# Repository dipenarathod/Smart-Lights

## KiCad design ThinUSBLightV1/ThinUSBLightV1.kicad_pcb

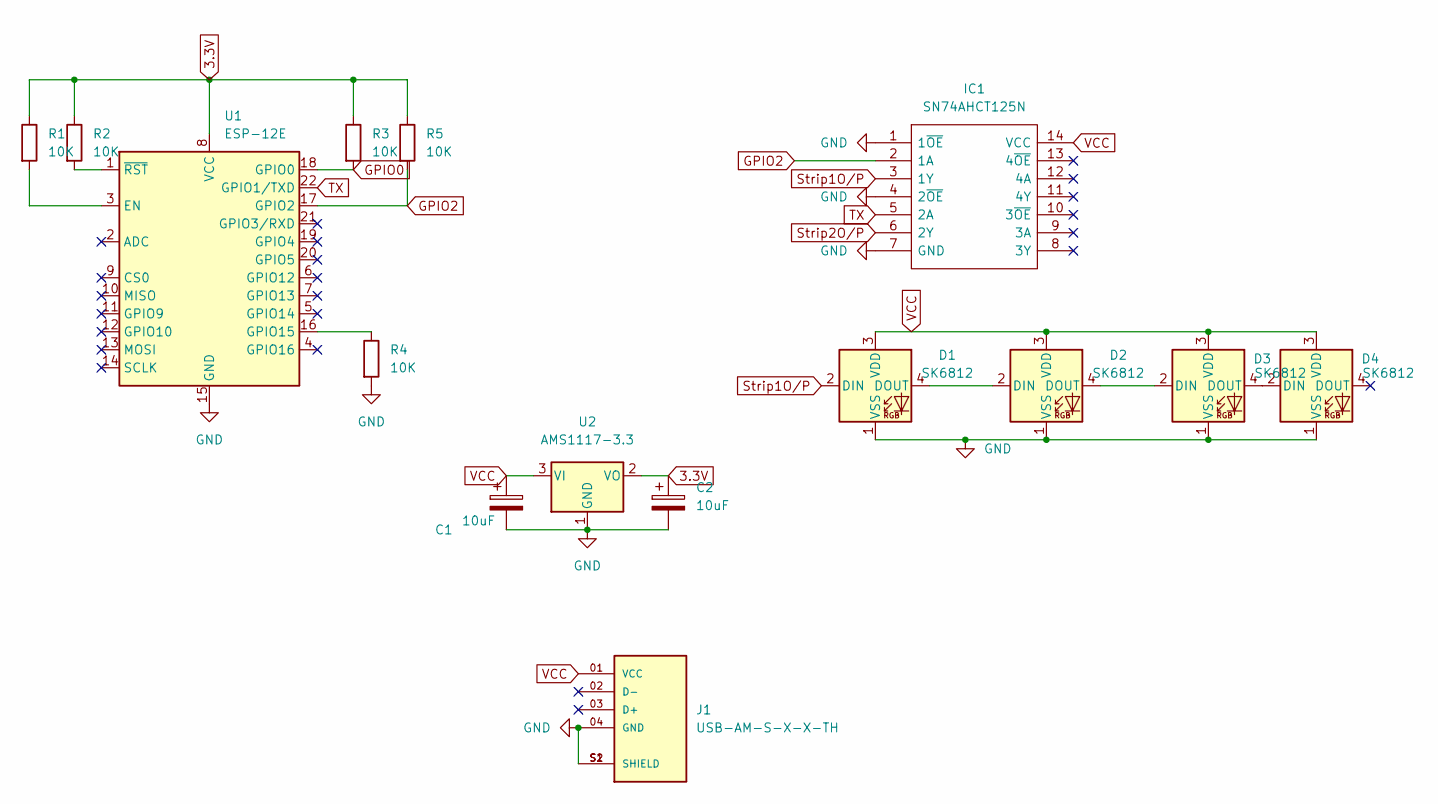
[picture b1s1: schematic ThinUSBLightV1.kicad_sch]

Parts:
C1, C2: 10uF; C_1206_3216Metric_Pad1.33x1.80mm_HandSolder
D1, D2, D3, D4: SK6812; LED_SK6812_PLCC4_5.0x5.0mm_P3.2mm
IC1: SN74AHCT125N; 74HC125D; Manufacturer_Part_Number SN74AHCT125N; Mouser Part Number 595-SN74AHCT125N
J1: USB-AM-S-X-X-TH; SAMTEC_USB-AM-S-X-X-TH; PARTREV U
R1, R2, R3, R4, R5: 10K; R_0805_2012Metric_Pad1.20x1.40mm_HandSolder
U1: ESP-12E
U2: AMS1117-3.3; SOT-223-3_TabPin2

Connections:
3.3V: C2.1, R1.1, R2.1, R3.1, R5.1, U1.8 (VCC), U2.2 (VO)
GND: C1.2, C2.2, D1.1 (VSS), D2.1 (VSS), D3.1 (VSS), D4.1 (VSS), IC1.1 (1~OE), IC1.4 (2~OE), IC1.7 (GND), J1.04 (GND), J1.S1 (SHIELD), J1.S2 (SHIELD), R4.2, U1.15 (GND), U2.1 (GND)
GPIO0: R3.2, U1.18 (GPIO0)
GPIO2: IC1.2 (1A), R5.2, U1.17 (GPIO2)
unnamed: D1.4 (DOUT), D2.2 (DIN)
unnamed: D2.4 (DOUT), D3.2 (DIN)
unnamed: D3.4 (DOUT), D4.2 (DIN)
unnamed: R1.2, U1.3 (EN)
unnamed: R2.2, U1.1 (~RST)
unnamed: R4.1, U1.16 (GPIO15)
Strip1O/P: D1.2 (DIN), IC1.3 (1Y)
Strip2O/P: IC1.6 (2Y)
TX: IC1.5 (2A), U1.22 (GPIO1/TXD)
VCC: C1.1, D1.3 (VDD), D2.3 (VDD), D3.3 (VDD), D4.3 (VDD), IC1.14 (VCC), J1.01 (VCC), U2.3 (VI)

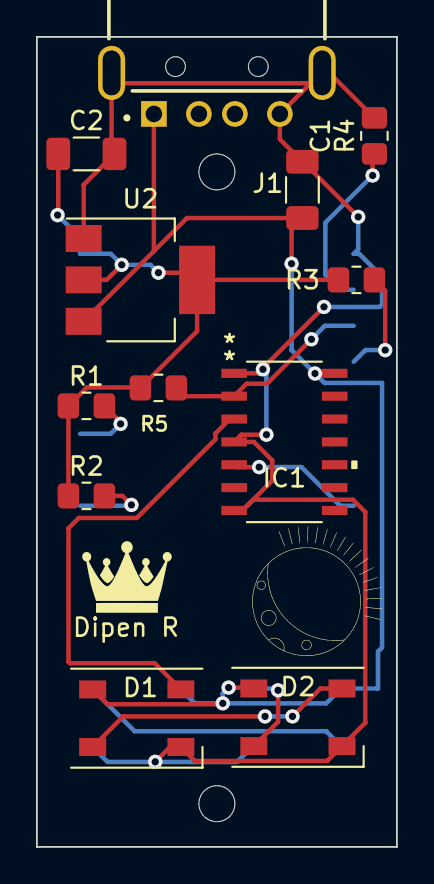
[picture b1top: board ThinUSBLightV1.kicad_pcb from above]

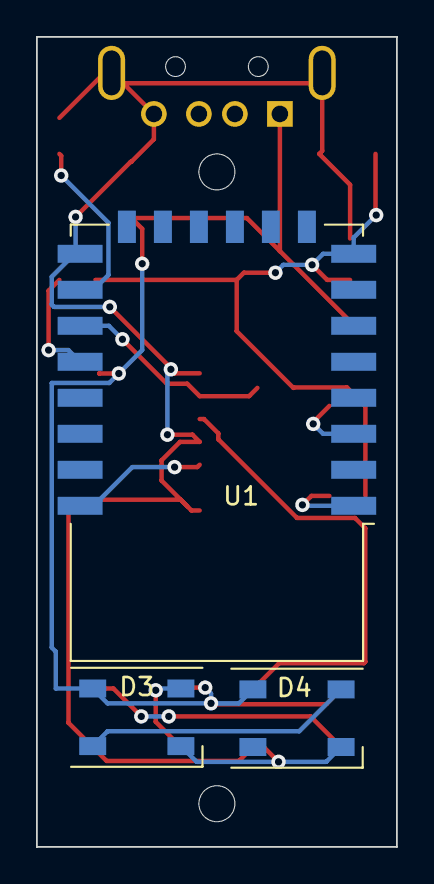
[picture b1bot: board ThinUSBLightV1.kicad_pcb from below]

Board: 2 copper layers, 20.0 x 45.0 mm, 15 parts (3 on the bottom side), 13 nets.

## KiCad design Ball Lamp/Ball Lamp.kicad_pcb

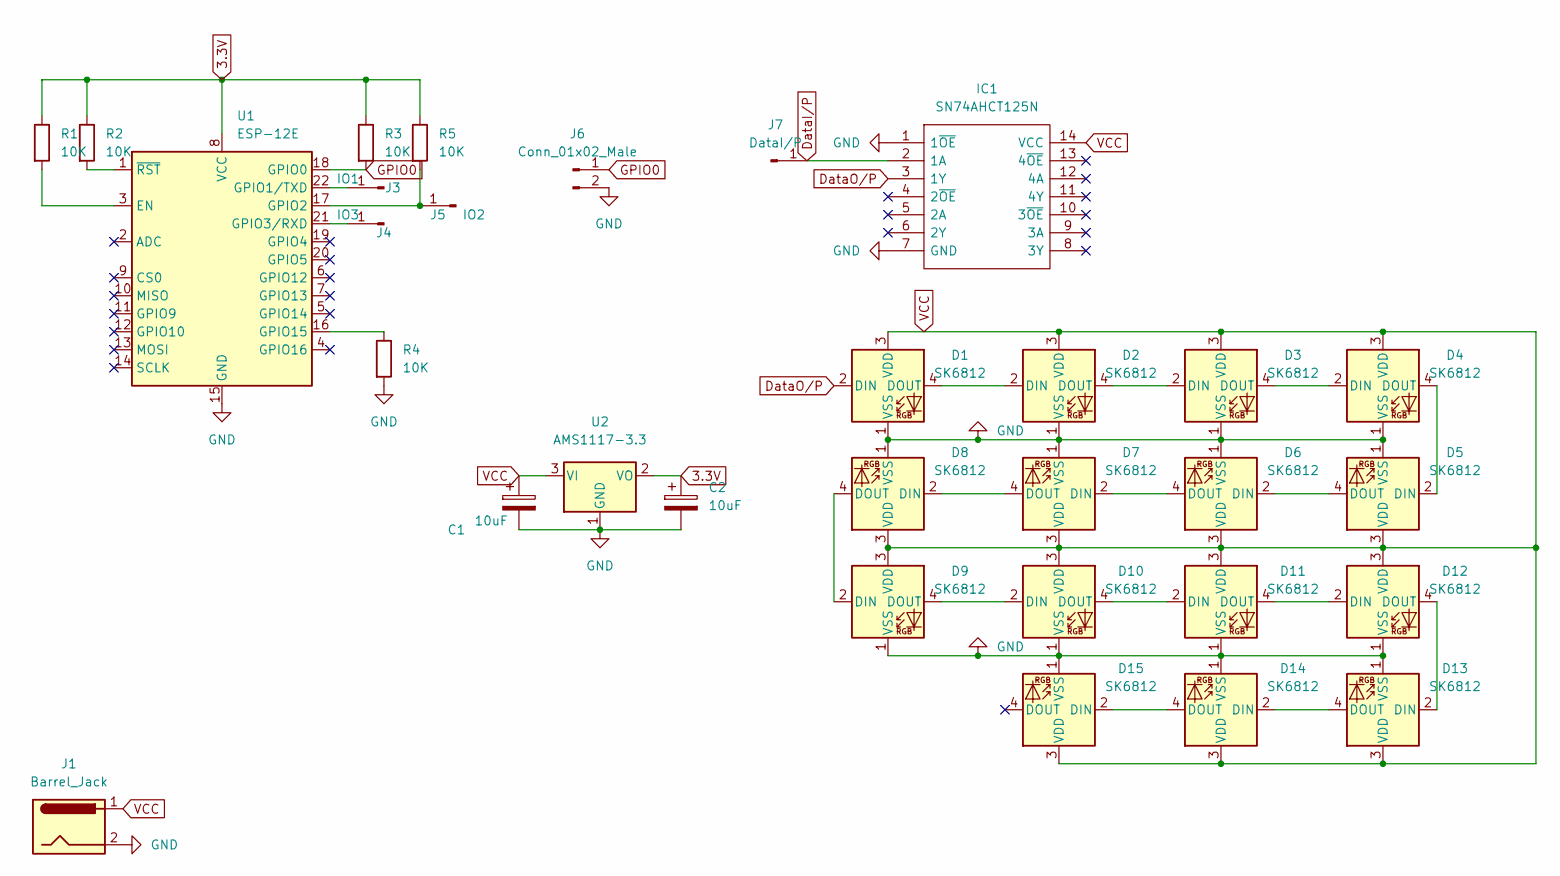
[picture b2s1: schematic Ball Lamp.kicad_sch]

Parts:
C1, C2: 10uF; CP_Radial_D5.0mm_P2.00mm
D1, D2, D3, D4, D5, D6, D7, D8, D9, D10, D11, D12, D13, D14, D15: SK6812; LED_SK6812_PLCC4_5.0x5.0mm_P3.2mm
IC1: SN74AHCT125N; DIP794W53P254L1930H508Q14N; Manufacturer_Part_Number SN74AHCT125N; Mouser Part Number 595-SN74AHCT125N
J1: Barrel_Jack; BarrelJack_GCT_DCJ200-10-A_Horizontal
J3: IO1; PinHeader_1x01_P2.54mm_Vertical
J4: IO3; PinHeader_1x01_P2.54mm_Vertical
J5: IO2; PinHeader_1x01_P2.54mm_Vertical
J6: Conn_01x02_Male; PinHeader_1x02_P2.54mm_Vertical
J7: DataI/P; PinHeader_1x01_P2.54mm_Vertical
R1, R2, R3, R4, R5: 10K; R_Axial_DIN0207_L6.3mm_D2.5mm_P7.62mm_Horizontal
U1: ESP-12E
U2: AMS1117-3.3; SOT-223-3_TabPin2

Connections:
3.3V: C2.1, R1.1, R2.1, R3.1, R5.1, U1.8 (VCC), U2.2 (VO)
DataI/P: IC1.2 (1A), J7.1
DataO/P: D1.2 (DIN), IC1.3 (1Y)
GND: C1.2, C2.2, D1.1 (VSS), D2.1 (VSS), D3.1 (VSS), D4.1 (VSS), D5.1 (VSS), D6.1 (VSS), D7.1 (VSS), D8.1 (VSS), D9.1 (VSS), D10.1 (VSS), D11.1 (VSS), D12.1 (VSS), D13.1 (VSS), D14.1 (VSS), D15.1 (VSS), IC1.1 (1~OE), IC1.7 (GND), J1.2, J6.2, R4.2, U1.15 (GND), U2.1 (GND); also elsewhere on the board
GPIO0: J6.1, R3.2, U1.18 (GPIO0)
unnamed: D1.4 (DOUT), D2.2 (DIN)
unnamed: D2.4 (DOUT), D3.2 (DIN)
unnamed: D3.4 (DOUT), D4.2 (DIN)
unnamed: D4.4 (DOUT), D5.2 (DIN)
unnamed: D5.4 (DOUT), D6.2 (DIN)
unnamed: D6.4 (DOUT), D7.2 (DIN)
unnamed: D7.4 (DOUT), D8.2 (DIN)
unnamed: D8.4 (DOUT), D9.2 (DIN)
unnamed: D9.4 (DOUT), D10.2 (DIN)
unnamed: D10.4 (DOUT), D11.2 (DIN)
unnamed: D11.4 (DOUT), D12.2 (DIN)
unnamed: D12.4 (DOUT), D13.2 (DIN)
unnamed: D13.4 (DOUT), D14.2 (DIN)
unnamed: D14.4 (DOUT), D15.2 (DIN)
unnamed: J3.1, U1.22 (GPIO1/TXD)
unnamed: J4.1, U1.21 (GPIO3/RXD)
unnamed: J5.1, R5.2, U1.17 (GPIO2)
unnamed: R1.2, U1.3 (EN)
unnamed: R2.2, U1.1 (~RST)
unnamed: R4.1, U1.16 (GPIO15)
VCC: C1.1, D1.3 (VDD), D2.3 (VDD), D3.3 (VDD), D4.3 (VDD), D5.3 (VDD), D6.3 (VDD), D7.3 (VDD), D8.3 (VDD), D9.3 (VDD), D10.3 (VDD), D11.3 (VDD), D12.3 (VDD), D13.3 (VDD), D14.3 (VDD), D15.3 (VDD), IC1.14 (VCC), J1.1, U2.3 (VI); also elsewhere on the board

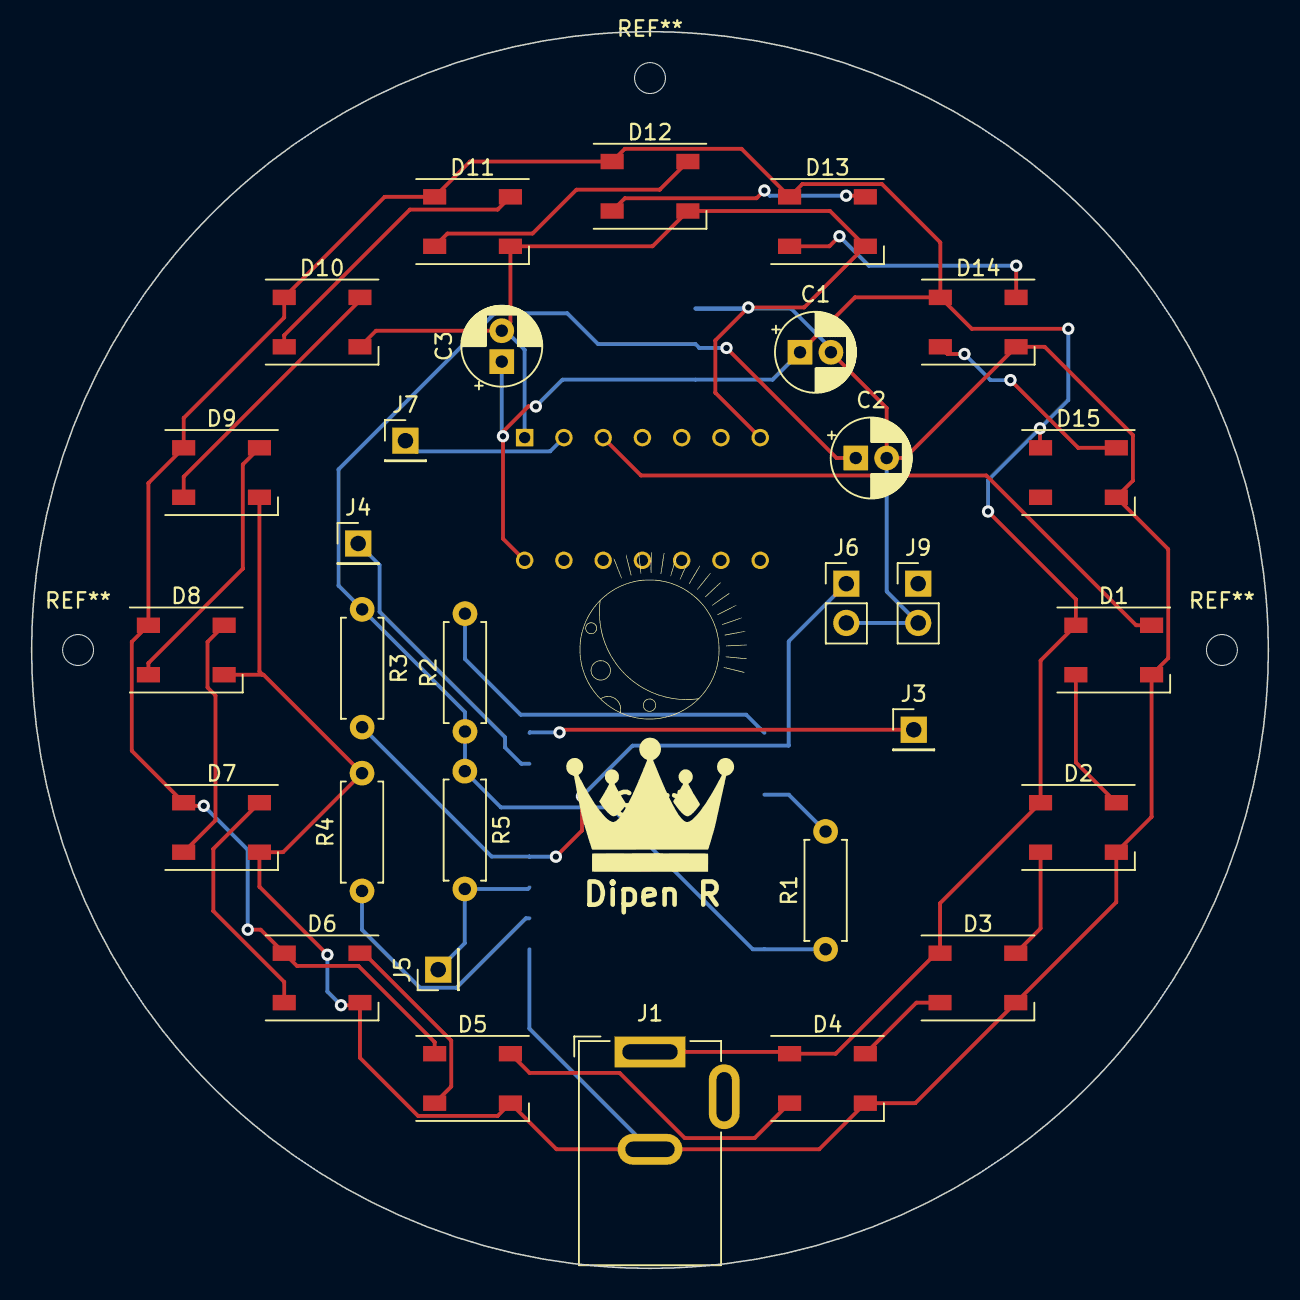
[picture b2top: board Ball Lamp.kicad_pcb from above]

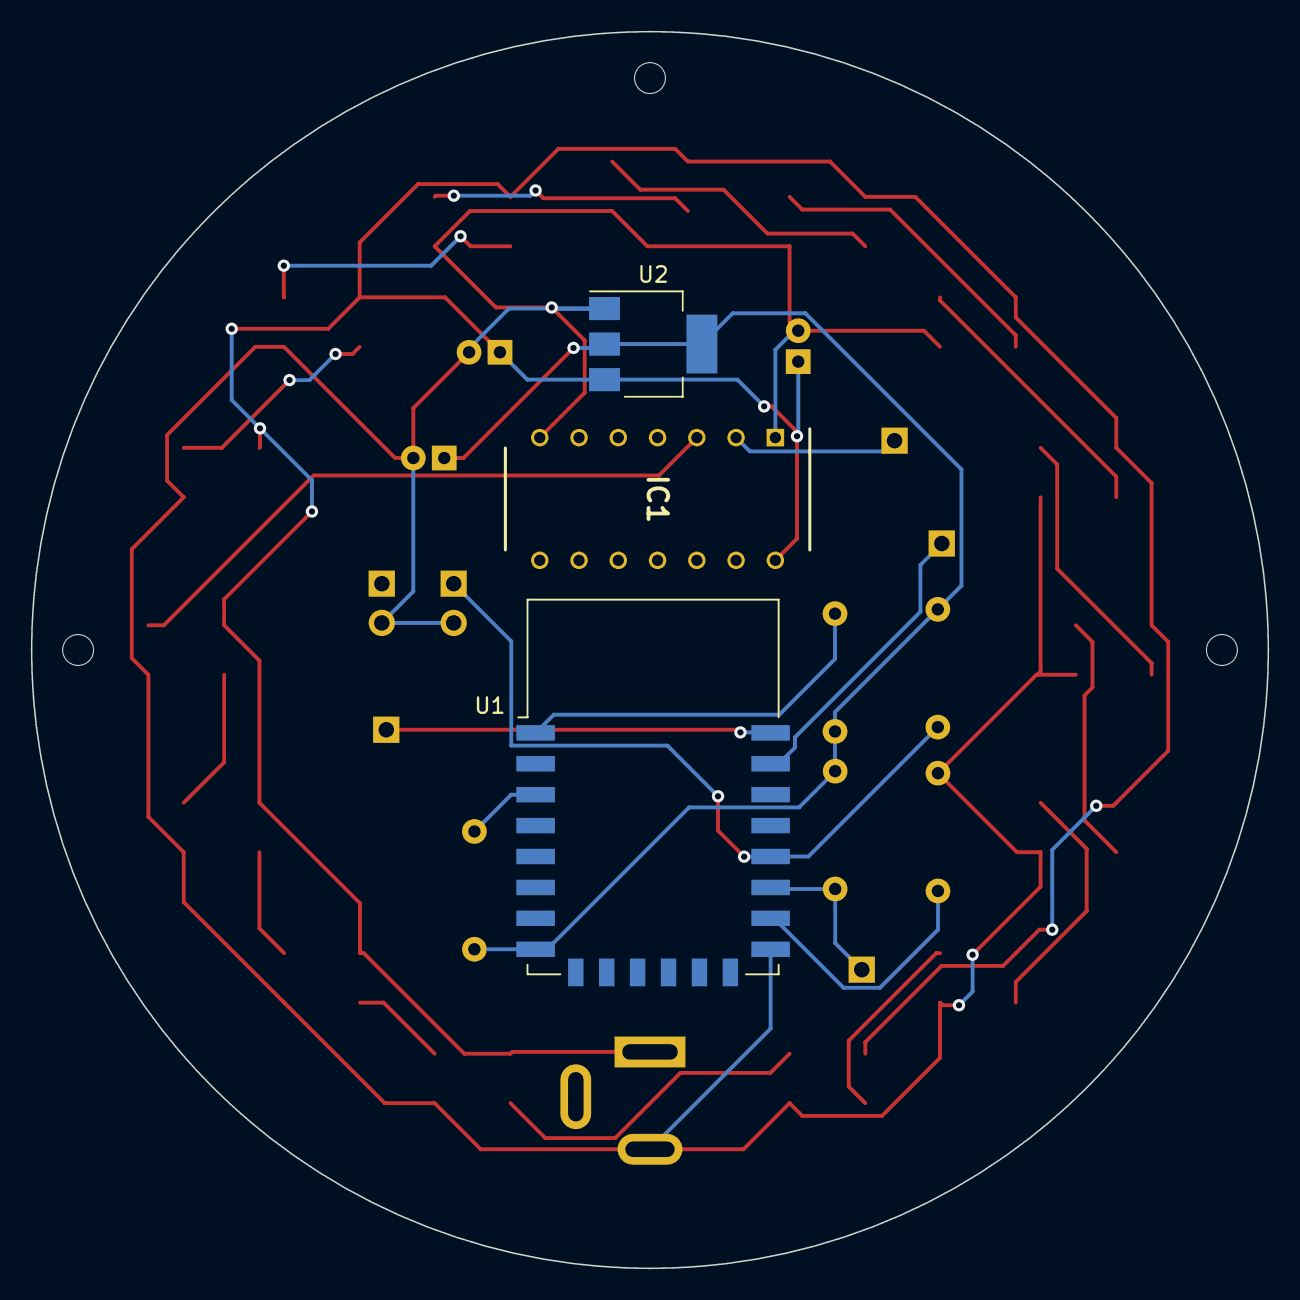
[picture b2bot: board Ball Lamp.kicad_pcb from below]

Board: 2 copper layers, 80.0 x 80.0 mm, 33 parts (3 on the bottom side), 26 nets.

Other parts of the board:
C3: 10 uF; CP_Radial_D5.0mm_P2.00mm
J9: Conn_01x02_Male; PinHeader_1x02_P2.54mm_Vertical

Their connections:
GND: C3.2, J9.2; also elsewhere on the board
VCC: C3.1; also elsewhere on the board

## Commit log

2022-11-09 USB Night Light V1
2025-05-22 Added Lights
2025-05-22 added images

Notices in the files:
parts and their libraries:
Copyright 2021 Accelerated Designs. All rights reserved.
